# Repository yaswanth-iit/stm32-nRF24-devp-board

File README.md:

# STM32-nRF24 RF devpelopment board
This repository contains STM32 nRF24 development board schematics, PCB layout, output files (Designed using kiCAD) [4-Layer]

[Schematics](https://raw.githubusercontent.com/yaswanth-iit/stm32-nRF24-devp-board/master/quick%20view/schematics-stm32-nrf24.pdf)

# Top View

# Bottom view

# PCB Layout

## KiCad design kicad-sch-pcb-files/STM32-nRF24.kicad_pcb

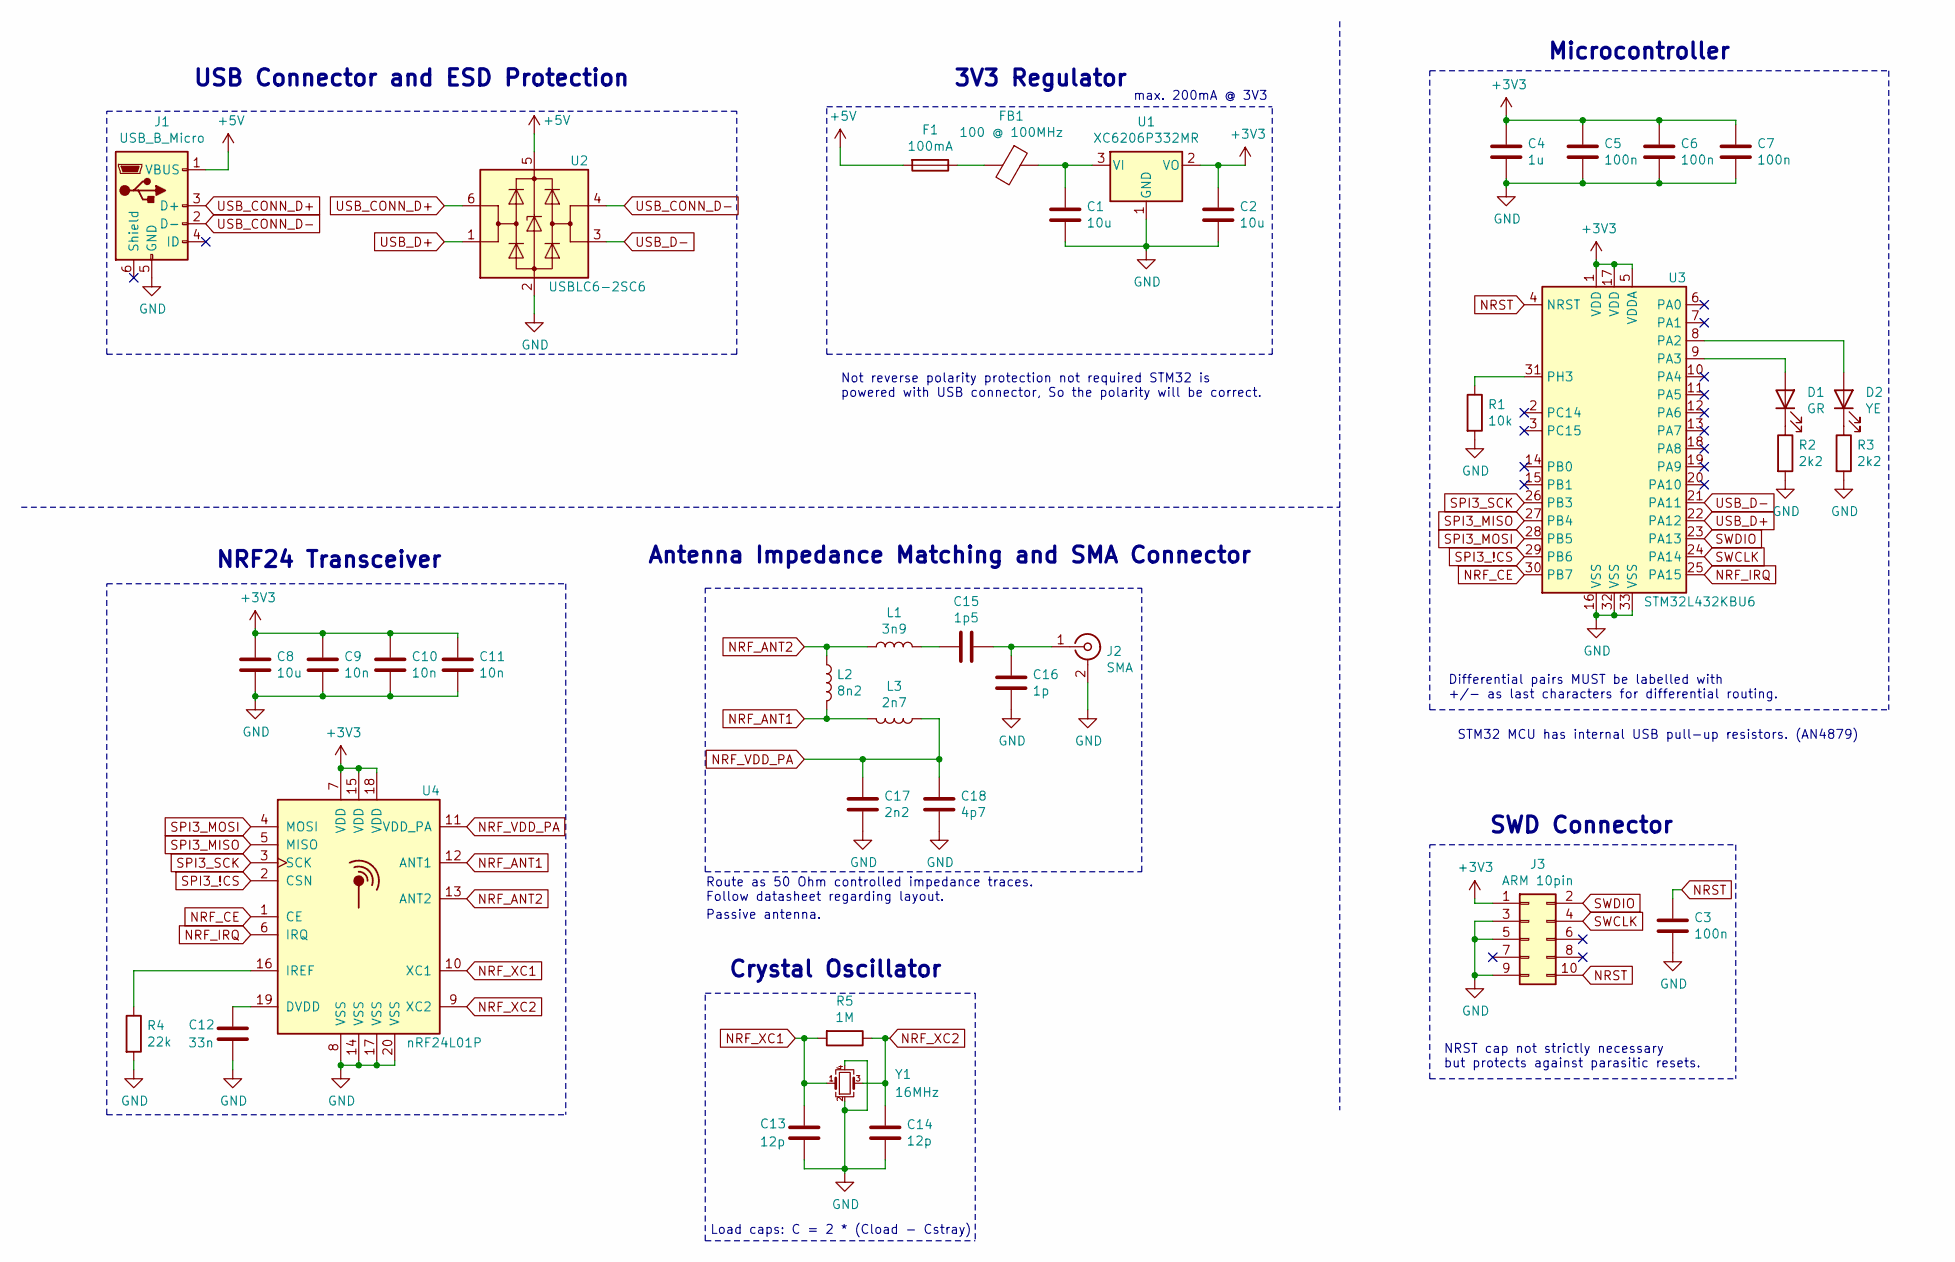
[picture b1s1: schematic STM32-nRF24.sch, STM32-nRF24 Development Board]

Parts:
C1, C2, C8: 10u; C_0603_1608Metric
C3, C5, C6, C7: 100n; C_0402_1005Metric
C4: 1u; C_0402_1005Metric
C9, C10, C11: 10n; C_0402_1005Metric
C12: 33n; C_0402_1005Metric
C13, C14: 12p; C_0402_1005Metric
C15: 1p5; C_0402_1005Metric
C16: 1p; C_0402_1005Metric
C17: 2n2; C_0402_1005Metric
C18: 4p7; C_0402_1005Metric
D1: GR; LED_0603_1608Metric
D2: YE; LED_0603_1608Metric
F1: 100mA; Fuse_1206_3216Metric
FB1: 100 @ 100MHz; L_0805_2012Metric
J1: USB_B_Micro; 101181930001LF
J2: SMA; SMA_Samtec_SMA-J-P-X-ST-EM1_EdgeMount
J3: ARM 10pin; PinHeader_2x05_P1.27mm_Vertical
L1: 3n9; L_0402_1005Metric
L2: 8n2; L_0402_1005Metric
L3: 2n7; L_0402_1005Metric
R1: 10k; R_0402_1005Metric
R2, R3: 2k2; R_0603_1608Metric
R4: 22k; R_0402_1005Metric
R5: 1M; R_0402_1005Metric
U1: XC6206P332MR; SOT-23
U2: USBLC6-2SC6; SOT-23-6
U3: STM32L432KBU6; QFN-32-1EP_5x5mm_P0.5mm_EP3.45x3.45mm
U4: nRF24L01P; QFN-20-1EP_4x4mm_P0.5mm_EP2.5x2.5mm
Y1: 16MHz; Crystal_SMD_3225-4Pin_3.2x2.5mm

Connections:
+3V3: C2.1, C4.1, C5.1, C6.1, C7.1, C8.1, C9.1, C10.1, C11.1, J3.1, U1.2 (VO), U3.1 (VDD), U3.5 (VDDA), U3.17 (VDD), U4.7 (VDD), U4.15 (VDD), U4.18 (VDD); also elsewhere on the board
+5V: F1.2, J1.1 (VBUS), U2.5 (VBUS); also elsewhere on the board
GND: C1.2, C2.2, C3.2, C4.2, C5.2, C6.2, C7.2, C8.2, C9.2, C10.2, C11.2, C12.2, C13.2, C14.2, C16.1, C17.1, C18.1, J1.5 (GND), J2.2 (Ext), J3.3, J3.5, J3.9, R1.2, R2.2, R3.2, R4.2, U1.1 (GND), U2.2 (GND), U3.16 (VSS), U3.32 (VSS), U3.33 (VSS), U4.8 (VSS), U4.14 (VSS), U4.17 (VSS), U4.20 (VSS), Y1.2, Y1.4
NRF_ANT1: L2.2, L3.2, U4.12 (ANT1)
NRF_ANT2: L1.1, L2.1, U4.13 (ANT2)
NRF_CE: U3.30 (PB7), U4.1 (CE)
NRF_IRQ: U3.25 (PA15), U4.6 (IRQ)
NRF_VDD_PA: C17.2, C18.2, L3.1, U4.11 (VDD_PA)
NRF_XC1: C13.1, R5.2, U4.10 (XC1), Y1.1
NRF_XC2: C14.1, R5.1, U4.9 (XC2), Y1.3
NRST: C3.1, J3.10, U3.4 (NRST)
unnamed: C1.1, FB1.1, U1.3 (VI)
unnamed: C12.1, U4.19 (DVDD)
unnamed: C15.1, C16.2, J2.1 (In)
unnamed: C15.2, L1.2
unnamed: D1.1 (K), R2.1
unnamed: D1.2 (A), U3.9 (PA3)
unnamed: D2.1 (K), R3.1
unnamed: D2.2 (A), U3.8 (PA2)
unnamed: F1.1, FB1.2
unnamed: R1.1, U3.31 (PH3)
unnamed: R4.1, U4.16 (IREF)
SPI3_!CS: U3.29 (PB6), U4.2 (CSN)
SPI3_MISO: U3.27 (PB4), U4.5 (MISO)
SPI3_MOSI: U3.28 (PB5), U4.4 (MOSI)
SPI3_SCK: U3.26 (PB3), U4.3 (SCK)
SWCLK: J3.4, U3.24 (PA14)
SWDIO: J3.2, U3.23 (PA13)
USB_CONN_D+: J1.3 (D+), U2.6 (I/O1)
USB_CONN_D-: J1.2 (D-), U2.4 (I/O2)
USB_D+: U2.1 (I/O1), U3.22 (PA12)
USB_D-: U2.3 (I/O2), U3.21 (PA11)

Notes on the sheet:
NRST cap not strictly necessary but protects against parasitic resets.
Differential pairs MUST be labelled with +/- as last characters for differential routing.
3V3 Regulator
Microcontroller
SWD Connector
STM32 MCU has internal USB pull-up resistors. (AN4879)
Not reverse polarity protection not required STM32 is powered with USB connector, So the polarity will be correct.
Load caps: C = 2 * (Cload - Cstray)
NRF24 Transceiver
Crystal Oscillator
USB Connector and ESD Protection
Antenna Impedance Matching and SMA Connector
Route as 50 Ohm controlled impedance traces. Follow datasheet regarding layout.
Passive antenna.
max. 200mA @ 3V3

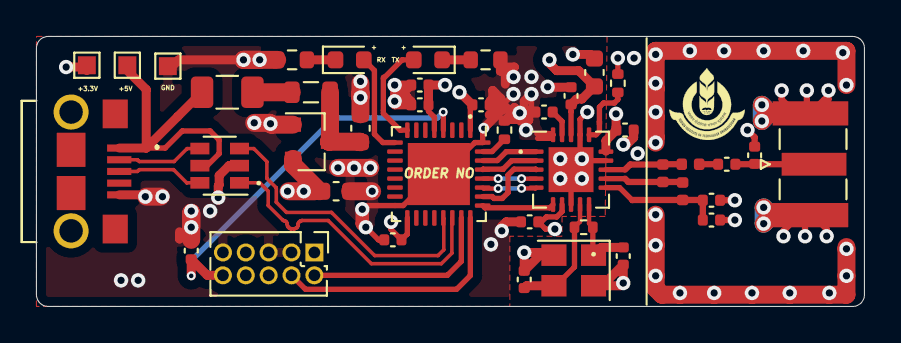
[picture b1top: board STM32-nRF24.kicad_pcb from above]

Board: 4 copper layers, 46.0 x 15.0 mm, 40 parts (0 on the bottom side), 32 nets.

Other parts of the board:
3v3, 5v: TestPoint_Pad_1.0x1.0mm

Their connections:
+3V3: 3v3.1; also elsewhere on the board
+5V: 5v.1; also elsewhere on the board

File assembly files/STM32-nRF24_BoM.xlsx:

| Item | Qty | Reference(s) | Value | Description | Component name : PCB footprint | Manufacturer | Part Number | Availability status | Distributor
 | 1 | 3 | C1, C2, C8, | 10u | Unpolarized capacitor | Capacitor_SMD:C_0603_1608Metric
 | 2 | 4 | C3, C5, C6, C7, | 100n | Unpolarized capacitor | Capacitor_SMD:C_0402_1005Metric
 | 3 | 1 | C4, | 1u | Unpolarized capacitor | Capacitor_SMD:C_0402_1005Metric
 | 4 | 3 | C9, C10, C11, | 10n | Unpolarized capacitor | Capacitor_SMD:C_0402_1005Metric
 | 5 | 1 | C12, | 33n | Unpolarized capacitor | Capacitor_SMD:C_0402_1005Metric
 | 6 | 2 | C13, C14, | 12p | Unpolarized capacitor | Capacitor_SMD:C_0402_1005Metric
 | 7 | 1 | C15, | 1p5 | Unpolarized capacitor | Capacitor_SMD:C_0402_1005Metric
 | 8 | 1 | C16, | 1p | Unpolarized capacitor | Capacitor_SMD:C_0402_1005Metric
 | 9 | 1 | C17, | 2n2 | Unpolarized capacitor | Capacitor_SMD:C_0402_1005Metric
 | 10 | 1 | C18, | 4p7 | Unpolarized capacitor | Capacitor_SMD:C_0402_1005Metric
 | 11 | 1 | D1, | GR | Light emitting diode | LED_SMD:LED_0603_1608Metric
 | 12 | 1 | D2, | YE | Light emitting diode | LED_SMD:LED_0603_1608Metric
 | 13 | 1 | F1, | 100mA | Fuse | Fuse:Fuse_1206_3216Metric
 | 14 | 1 | FB1, | 100 @ 100MHz | Ferrite bead | Inductor_SMD:L_0805_2012Metric
 | 15 | 1 | J1, | USB_B_Micro | USB Micro Type B connector | 10118193-0001LF:101181930001LF
 | 16 | 1 | J2, | SMA | coaxial connector (BNC, SMA, SMB, SMC, Cinch/RCA, ...) | Connector_Coaxial:SMA_Samtec_SMA-J-P-X-ST-EM1_EdgeMount
 | 17 | 1 | J3, | ARM 10pin | Generic connector, double row, 02x05, odd/even pin numbering scheme (row 1 odd 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 | Connector_PinHeader_1.27mm:PinHeader_2x05_P1.27mm_Vertical
 | 18 | 1 | L1, | 3n9 | Inductor | Inductor_SMD:L_0402_1005Metric
 | 19 | 1 | L2, | 8n2 | Inductor | Inductor_SMD:L_0402_1005Metric
 | 20 | 1 | L3, | 2n7 | Inductor | Inductor_SMD:L_0402_1005Metric
 | 21 | 1 | R1, | 10k | Resistor | Resistor_SMD:R_0402_1005Metric
 | 22 | 2 | R2, R3, | 2k2 | Resistor | Resistor_SMD:R_0603_1608Metric
 | 23 | 1 | R4, | 22k | Resistor | Resistor_SMD:R_0402_1005Metric
 | 24 | 1 | R5, | 1M | Resistor | Resistor_SMD:R_0402_1005Metric
 | 25 | 1 | U1, | XC6206P332MR | Positive 60-250mA Low Dropout Regulator, Fixed Output, SOT-23 | Package_TO_SOT_SMD:SOT-23
 | 26 | 1 | U2, | USBLC6-2SC6 | Very low capacitance ESD protection diode, 2 data-line, SOT-23-6 | Package_TO_SOT_SMD:SOT-23-6
 | 27 | 1 | U3, | STM32L432KBU6 | ARM Cortex-M4 MCU, 128KB flash, 64KB RAM, 80MHz, 1.71-3.6V, 26 GPIO, UFQFPN-32 | Package_DFN_QFN:QFN-32-1EP_5x5mm_P0.5mm_EP3.45x3.45mm
 | 28 | 1 | U4, | nRF24L01P | nRF24L01+, Ultra low power 2.4GHz RF Transceiver, QFN20 4x4mm | Package_DFN_QFN:QFN-20-1EP_4x4mm_P0.5mm_EP2.5x2.5mm
 | 29 | 1 | Y1, | 16MHz | Four pin crystal, GND on pins 2 and 4, small symbol | Crystal:Crystal_SMD_3225-4Pin_3.2x2.5mm

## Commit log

2021-11-07 Created ReadMe
